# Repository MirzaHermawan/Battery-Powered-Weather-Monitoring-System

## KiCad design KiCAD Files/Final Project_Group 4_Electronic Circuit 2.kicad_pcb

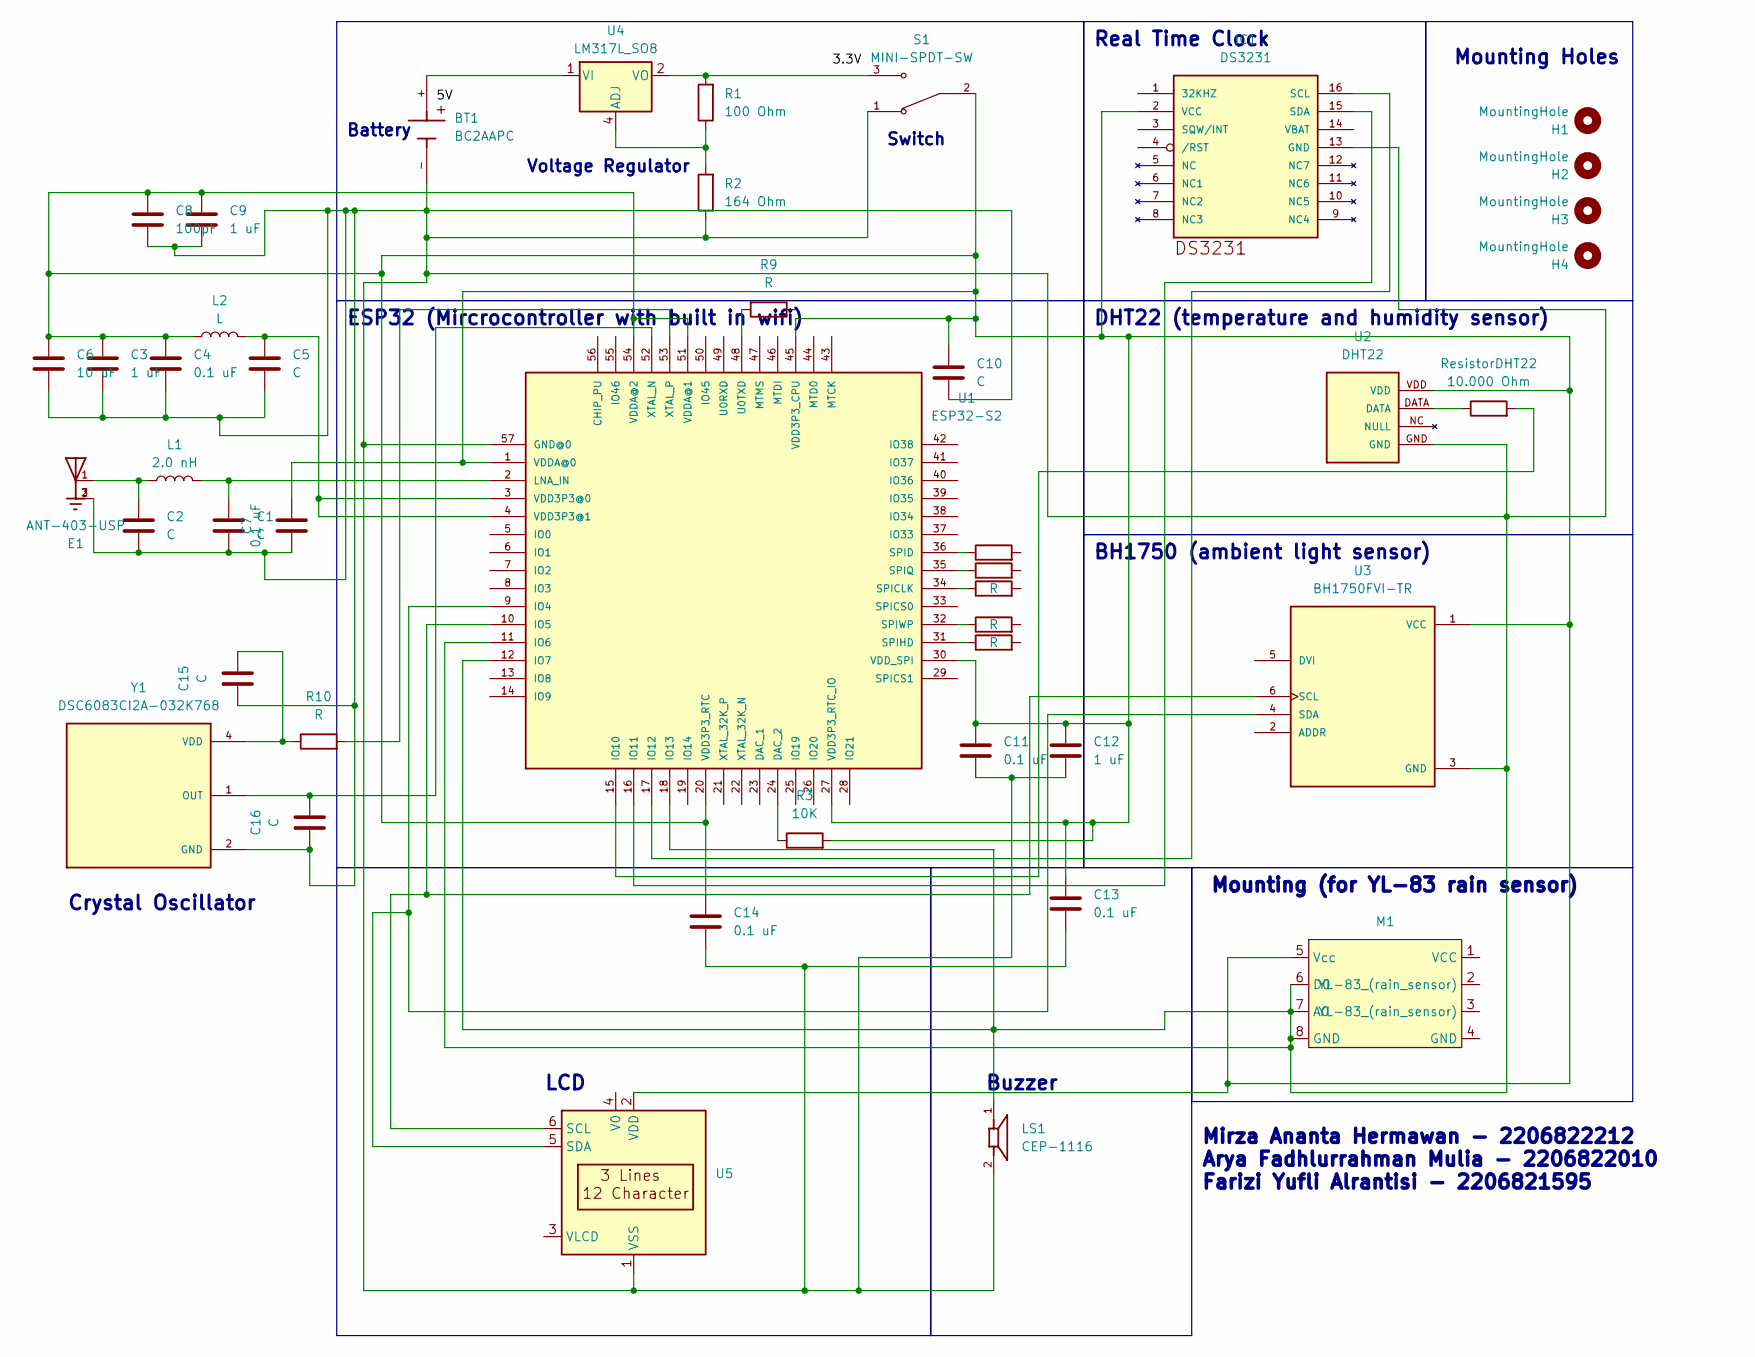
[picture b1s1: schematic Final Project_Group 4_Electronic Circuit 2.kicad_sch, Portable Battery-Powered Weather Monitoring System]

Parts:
BT1: BC2AAPC; BAT_BC2AAPC; PARTREV M
C1, C2, C5, C15, C16: C; L_1206_3216Metric
C3, C9, C12: 1 uF; L_1206_3216Metric
C4, C7, C11, C13, C14: 0.1 uF; L_1206_3216Metric
C6: 10 uF; L_1206_3216Metric
C8: 100pF; L_1206_3216Metric
C10: C; C_0201_0603Metric
E1: ANT-403-USP; XDCR_ANT-403-USP; PARTREV 1/3/2017
H1, H2, H3, H4: MountingHole; MountingHole_2.1mm
IC1: DS3231; SO16W
L1: 2.0 nH; L_1206_3216Metric
L2: L; L_1206_3216Metric
LS1: CEP-1116; CUI_CEP-1116
M1: Mounting1
R1: 100 Ohm; R_0201_0603Metric
R2: 164 Ohm; R_0201_0603Metric
R3: 10K; R_0201_0603Metric
R4, R5, R6, R7, R8, R9, R10: R; R_0201_0603Metric
ResistorDHT22: 10.000 Ohm; R_0201_0603Metric
S1: MINI-SPDT-SW; SW_MINI-SPDT-SW; PARTREV C
U1: ESP32-S2; QFN40P700X700X90-57T400N; MANUFACTURER_PART_NUMBE ESP32-S2
U2: DHT22
U3: BH1750FVI-TR; XDCR_BH1750FVI-TR; PARTREV D
U4: LM317L_SO8; SOIC-8_3.9x4.9mm_P1.27mm
U5: EA_T123X-I2C
Y1: DSC6083CI2A-032K768; OSC_DSC6083CI2A-032K768; PARTREV B

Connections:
unnamed: C2.1, E1.1, L1.1
unnamed: IC1.16 (SCL), U1.17 (IO12)
unnamed: IC1.15 (SDA), U1.16 (IO11)
unnamed: C3.1, C4.1, C6.1, C7.2, C8.1, C9.1, C10.1, C11.1, C12.1, C13.1, C14.1, IC1.2 (VCC), L2.1, M1.5 (Vcc), R3.2, S1.2, U1.1 (VDDA@0), U1.20 (VDD3P3_RTC), U1.27 (VDD3P3_RTC_IO), U1.30 (VDD_SPI), U1.45 (VDD3P3_CPU), U1.51 (VDDA@1), U1.54 (VDDA@2), U2.VDD, U3.1 (VCC), U5.2 (VDD)
unnamed: R1.2, S1.3, U4.2 (VO), U4.3 (VO), U4.6 (VO), U4.7 (VO)
unnamed: ResistorDHT22.1, U2.DATA
unnamed: R3.1, U1.24 (DAC_2)
unnamed: U1.9 (IO4), U3.4 (SDA), U5.5 (SDA)
unnamed: U1.10 (IO5), U3.6 (SCL), U5.6 (SCL)
unnamed: ResistorDHT22.2, U1.15 (IO10)
unnamed: C1.1, L1.2, U1.2 (LNA_IN)
unnamed: R6.1, U1.34 (SPICLK)
unnamed: R4.1, U1.36 (SPID)
unnamed: R8.1, U1.31 (SPIHD)
unnamed: R5.1, U1.35 (SPIQ)
unnamed: R7.1, U1.32 (SPIWP)
unnamed: R9.2, U1.48 (U0TXD)
unnamed: C5.1, L2.2, U1.3 (VDD3P3@0), U1.4 (VDD3P3@1)
unnamed: C16.2, U1.52 (XTAL_N), Y1.1 (OUT)
unnamed: R10.2, U1.53 (XTAL_P)
unnamed: R1.1, R2.2, U4.4 (ADJ)
unnamed: BT1.+, U4.1 (VI)
unnamed: C15.2, R10.1, Y1.4 (VDD)

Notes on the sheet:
DHT22 (temperature and humidity sensor)
Mirza Ananta Hermawan - 2206822212 Arya Fadhlurrahman Mulia - 2206822010 Farizi Yufli Alrantisi - 2206821595
Mounting Holes
BH1750 (ambient light sensor)
Crystal Oscillator
Mounting (for YL-83 rain sensor)
Voltage Regulator
Buzzer
Battery
LCD
Switch
Real Time Clock
ESP32 (Mircrocontroller with built in wifi)

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
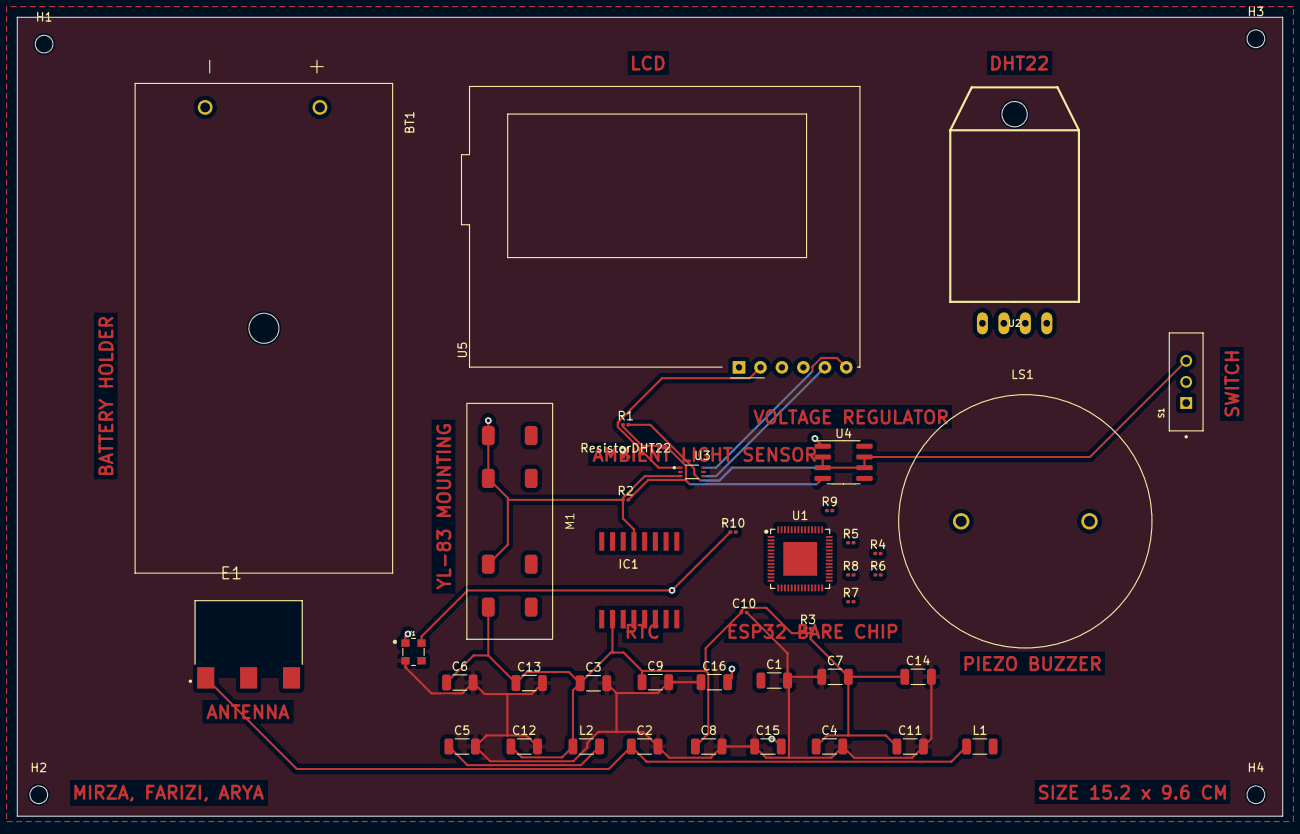
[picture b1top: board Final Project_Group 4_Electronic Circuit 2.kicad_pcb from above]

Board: 4 copper layers, 149.9 x 94.6 mm, 45 parts (0 on the bottom side), 26 nets.
